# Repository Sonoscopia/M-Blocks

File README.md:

# M-Blocks
Modular MIDI Controllers

## INFO
M-Blocks is a projected developed by Sonoscopia Associação Cultural (www.sonoscopia.pt). 
It consists of several MIDI controllers (M-Controllers) that can be patched to a receiving interface (M-Brain) in a modular fashion, that is, connecting an arbitrary number (32 max.) and type of controllers such as buttons, knobs, faders, encoders, etc. 
The M-Brain than receives data from all the controllers via and maps them to MIDI messages sent to the output, either through USB (future implementation) or MIDI DIN connections.
The communication between modules is made using I2C (Inter-Integrated Circuit) using the Arduino platform (www.arduino.cc).  

### Note to programmers
When programming an M-Brain for the first time do not forget to set the EEPROM memory using /utilities/EEPROM_Preset_Clear/

## CHANGELOG

### version 0.1.2 (phobosfeijoada)
Fully functional M-Brain prototype and M-Controllers.
Continuous controls (ex: knobs) can now output notes, [see commit](https://github.com/Sonoscopia/M-Blocks/commit/bef133f0ddcc1b52bf48fc73a7da5345fef3f352).
M-Toggle code was modified to (MToggleAsButton) acting as M-Button to work with Phobos.
There are still some bugs when programming M-Brain but it works as long as one follows the manual and pays attention to the LED's.

### version 0.1.1 (francesinha)
Fully functional M-Brain prototype and M-Controllers. Needs testing...

### version 0.1.0 (protobrain)
First working version for M-Brain protoype version (the version with LED's instead of a screen). 

### version 0.0.3 (gopro)
As the code for M-Brain is getting bigger I moved the code development to Atmel Studio. In the 'firmware' folder should be a version to compile in Arduino IDE for those of you who don't have Atmel Studio. 

### version 0.0.2 (whoisthemaster)
Inverted Master/Slave relationship. 
Now M-Brain is the slave and M-Controllers are masters.
This way the controllers send data whenever their hardware sensor data changes, while the slave (M-Brain) is requested to read this data. 

### version 0.0.1 (first prototype)
First working sketch containing two modules (MBrain and MToggle).
In this version the controller (MToggle) acts as a Slave device and MBrain acts as a Master device, where the slave is constantly sending data to the master with a flag to let the master know if data has changed or not. 

## CONTRIBUTORS 
Contributors: Gustavo Costa, Tiago Ângelo, Rui Dias, Ján Solčáni and PierrePierrePierre.

## DEPENDENCIES & ACKNOWLEDGEMENTS
- Wire library (https://www.arduino.cc/en/reference/wire) 
- EEPROM library (https://www.arduino.cc/en/Reference/EEPROM)
- Rotary library by Ben Buxton(https://github.com/brianlow/Rotary)
- MIDI Library by François Best (https://github.com/FortySevenEffects/arduino_midi_library)
- TimerOne Library (https://www.arduino.cc/reference/en/libraries/timerone/)

## LICENSE
[![CC BY-NC 4.0][cc-by-nc-shield]][cc-by-nc]

This work is licensed under a
[Creative Commons Attribution-NonCommercial 4.0 International License][cc-by-nc].

[![CC BY-NC 4.0][cc-by-nc-image]][cc-by-nc]

[cc-by-nc]: https://creativecommons.org/licenses/by-nc/4.0/
[cc-by-nc-image]: https://licensebuttons.net/l/by-nc/4.0/88x31.png
[cc-by-nc-shield]: https://img.shields.io/badge/License-CC%20BY--NC%204.0-lightgrey.svg

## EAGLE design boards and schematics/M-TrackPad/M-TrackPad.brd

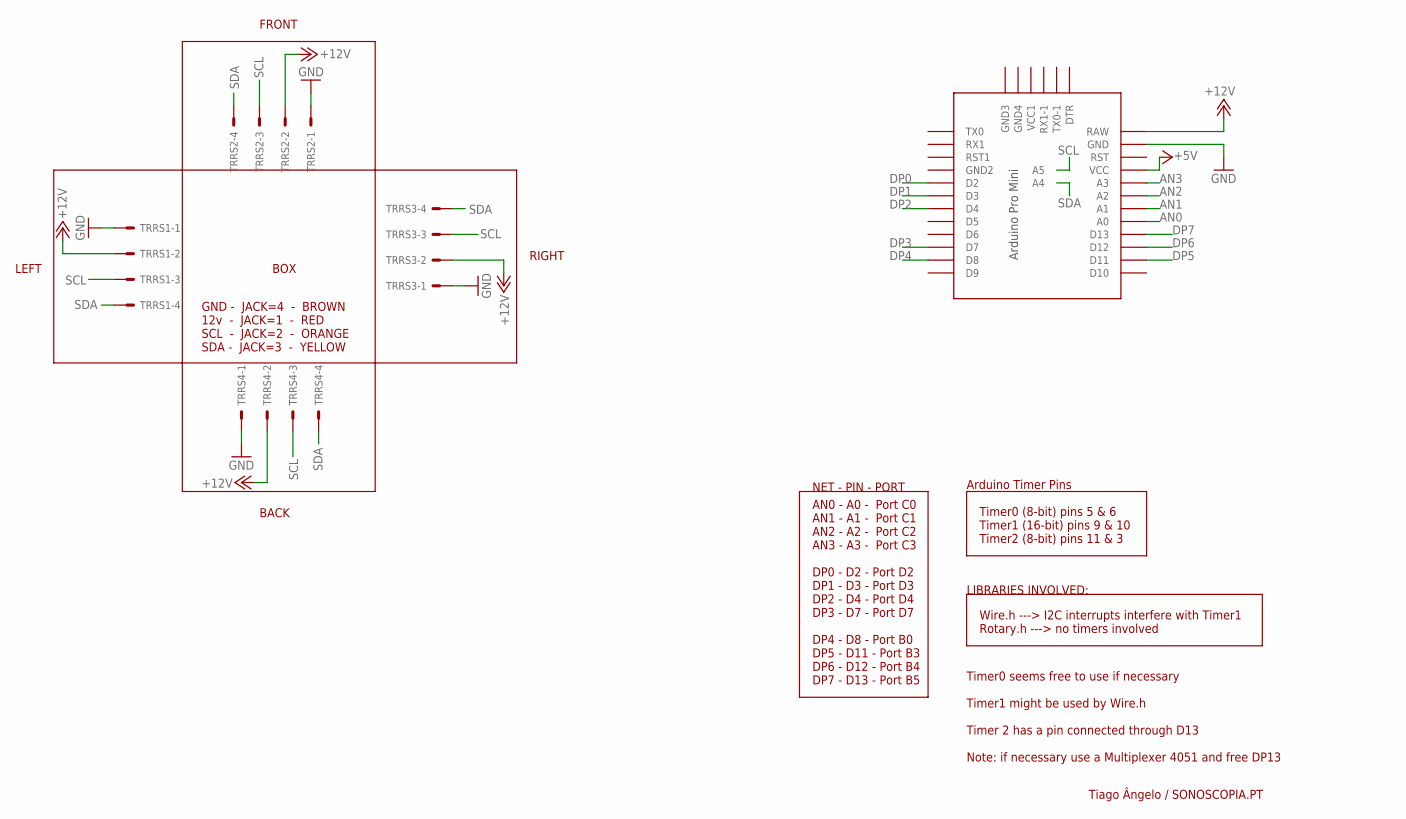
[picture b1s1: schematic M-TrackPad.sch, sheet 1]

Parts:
TRRS1, TRRS2, TRRS3, TRRS4: 22-27-2041-04; 6410-04
U$1: PRO-MINI-2

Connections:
+5V: U$1.VCC; also elsewhere on the board
+12V: TRRS1.2, TRRS2.2, TRRS3.2, TRRS4.2, U$1.RAW
AN0: U$1.A0
AN1: U$1.A1
AN2: U$1.A2
AN3: U$1.A3
DP0: U$1.D2; also elsewhere on the board
DP1: U$1.D3
DP2: U$1.D4
DP3: U$1.D7
DP4: U$1.D8
DP5: U$1.D11
DP6: U$1.D12
DP7: U$1.D13
GND: TRRS1.1, TRRS2.1, TRRS3.1, TRRS4.1, U$1.GND; also elsewhere on the board
SCL: TRRS1.3, TRRS2.3, TRRS3.3, TRRS4.3, U$1.A5; also elsewhere on the board
SDA: TRRS1.4, TRRS2.4, TRRS3.4, TRRS4.4, U$1.A4; also elsewhere on the board

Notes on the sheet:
Timer0 (8-bit) pins 5 & 6 Timer1 (16-bit) pins 9 & 10 Timer2 (8-bit) pins 11 & 3
Arduino Timer Pins
AN0 - A0 - Port C0 AN1 - A1 - Port C1 AN2 - A2 - Port C2 AN3 - A3 - Port C3 DP0 - D2 - Port D2 DP1 - D3 - Port D3 DP2 - D4 - Port D4 DP3 - D7 - Port D7 DP4 - D8 - Port B0 DP5 - D11 - Port B3 DP6 - D12 - Port B4 DP7 - D13 - Port B5
Wire.h ---> I2C interrupts interfere with Timer1 Rotary.h ---> no timers involved
LIBRARIES INVOLVED:
NET - PIN - PORT
Timer0 seems free to use if necessary Timer1 might be used by Wire.h Timer 2 has a pin connected through D13 Note: if necessary use a Multiplexer 4051 and free DP13
BOX
FRONT
RIGHT
LEFT
BACK
GND - JACK=4 - BROWN 12v - JACK=1 - RED SCL - JACK=2 - ORANGE SDA - JACK=3 - YELLOW
Tiago Ângelo / SONOSCOPIA.PT

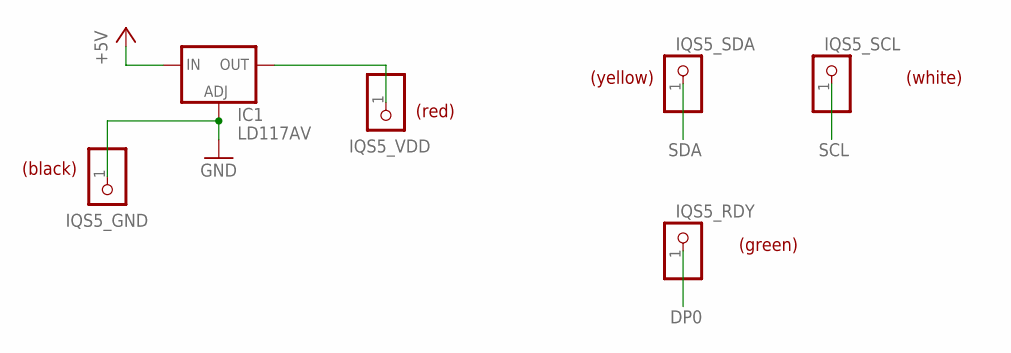
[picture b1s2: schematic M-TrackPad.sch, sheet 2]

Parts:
IC1: LD117AV; TO220L1
IQS5_GND, IQS5_RDY, IQS5_SCL, IQS5_SDA, IQS5_VDD: PINHD-1X1; 1X01

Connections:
+5V: IC1.3 (IN); also elsewhere on the board
DP0: IQS5_RDY.1; also elsewhere on the board
GND: IC1.1 (ADJ), IQS5_GND.1; also elsewhere on the board
unnamed: IC1.2 (OUT), IQS5_VDD.1
SCL: IQS5_SCL.1; also elsewhere on the board
SDA: IQS5_SDA.1; also elsewhere on the board

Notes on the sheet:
(black)
(red)
(yellow)
(white)
(green)

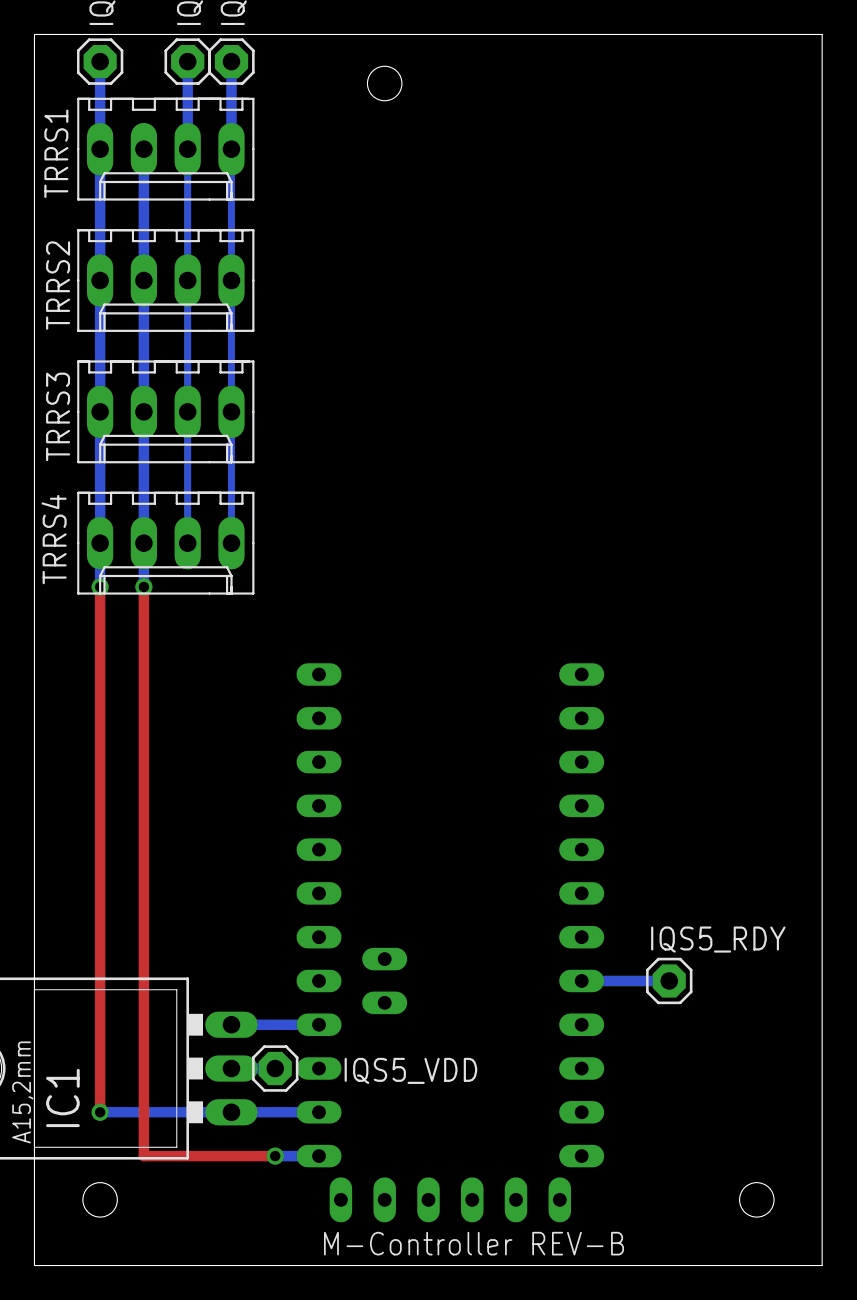
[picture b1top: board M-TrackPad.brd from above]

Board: 2 copper layers, 45.7 x 71.4 mm, 11 parts (0 on the bottom side), 7 nets.

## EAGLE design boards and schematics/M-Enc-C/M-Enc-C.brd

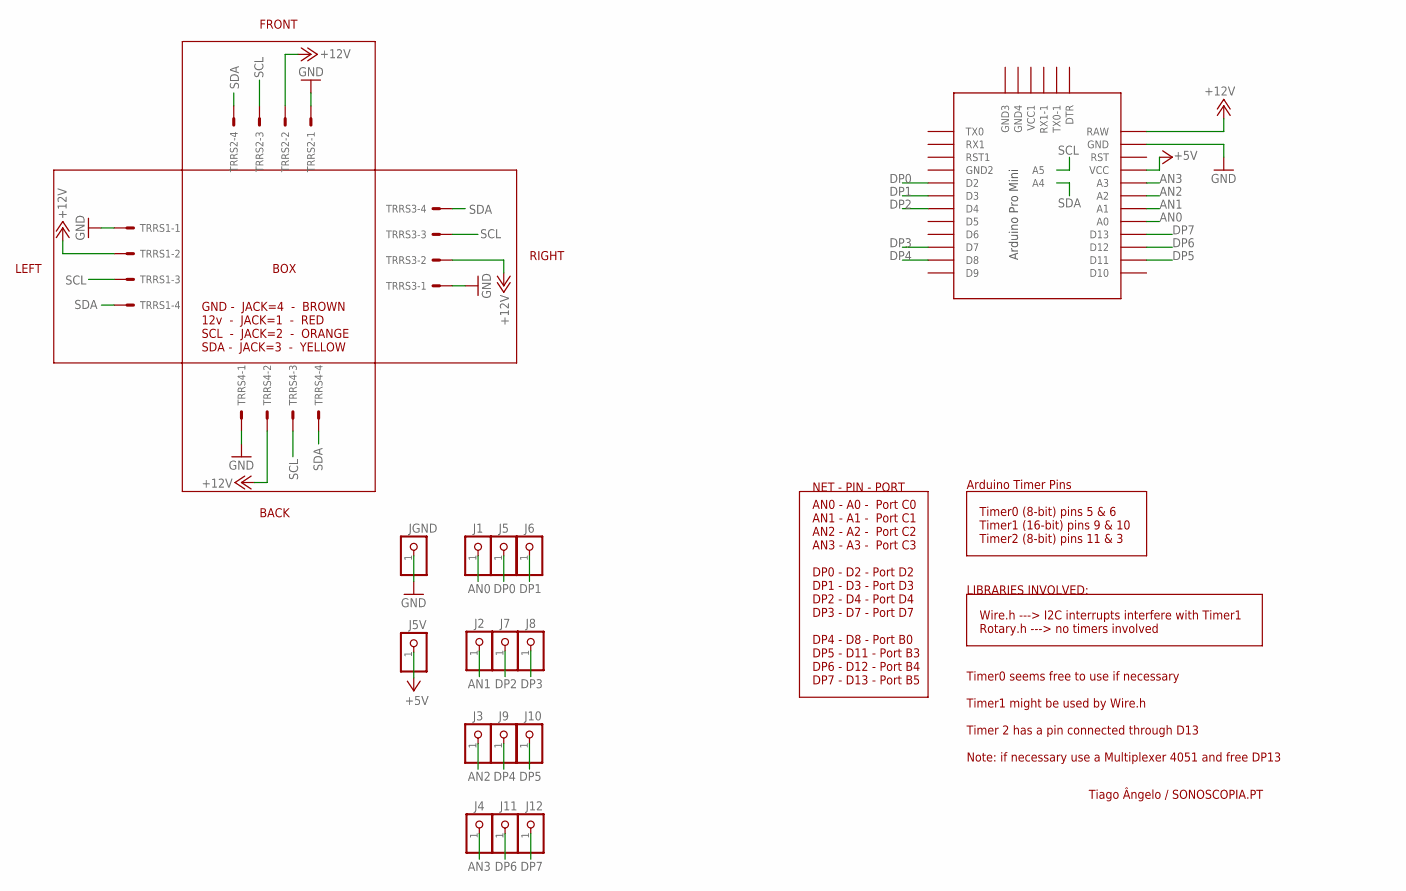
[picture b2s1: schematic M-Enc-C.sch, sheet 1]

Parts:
J1, J2, J3, J4, J5, J5V, J6, J7, J8, J9, J10, J11, J12: PINHD-1X1; 1X01
JGND: PINHD-1X1; 1X01
TRRS1, TRRS2, TRRS3, TRRS4: 22-27-2041-04; 6410-04
U$1: PRO-MINI-2

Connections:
+5V: J5V.1, U$1.VCC
+12V: TRRS1.2, TRRS2.2, TRRS3.2, TRRS4.2, U$1.RAW
AN0: J1.1, U$1.A0
AN1: J2.1, U$1.A1
AN2: J3.1, U$1.A2
AN3: J4.1, U$1.A3
DP0: J5.1, U$1.D2
DP1: J6.1, U$1.D3
DP2: J7.1, U$1.D4
DP3: J8.1, U$1.D7
DP4: J9.1, U$1.D8
DP5: J10.1, U$1.D11
DP6: J11.1, U$1.D12
DP7: J12.1, U$1.D13
GND: JGND.1, TRRS1.1, TRRS2.1, TRRS3.1, TRRS4.1, U$1.GND
SCL: TRRS1.3, TRRS2.3, TRRS3.3, TRRS4.3, U$1.A5
SDA: TRRS1.4, TRRS2.4, TRRS3.4, TRRS4.4, U$1.A4

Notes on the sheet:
Timer0 (8-bit) pins 5 & 6 Timer1 (16-bit) pins 9 & 10 Timer2 (8-bit) pins 11 & 3
Arduino Timer Pins
AN0 - A0 - Port C0 AN1 - A1 - Port C1 AN2 - A2 - Port C2 AN3 - A3 - Port C3 DP0 - D2 - Port D2 DP1 - D3 - Port D3 DP2 - D4 - Port D4 DP3 - D7 - Port D7 DP4 - D8 - Port B0 DP5 - D11 - Port B3 DP6 - D12 - Port B4 DP7 - D13 - Port B5
Wire.h ---> I2C interrupts interfere with Timer1 Rotary.h ---> no timers involved
LIBRARIES INVOLVED:
NET - PIN - PORT
Timer0 seems free to use if necessary Timer1 might be used by Wire.h Timer 2 has a pin connected through D13 Note: if necessary use a Multiplexer 4051 and free DP13
BOX
FRONT
RIGHT
LEFT
BACK
GND - JACK=4 - BROWN 12v - JACK=1 - RED SCL - JACK=2 - ORANGE SDA - JACK=3 - YELLOW
Tiago Ângelo / SONOSCOPIA.PT

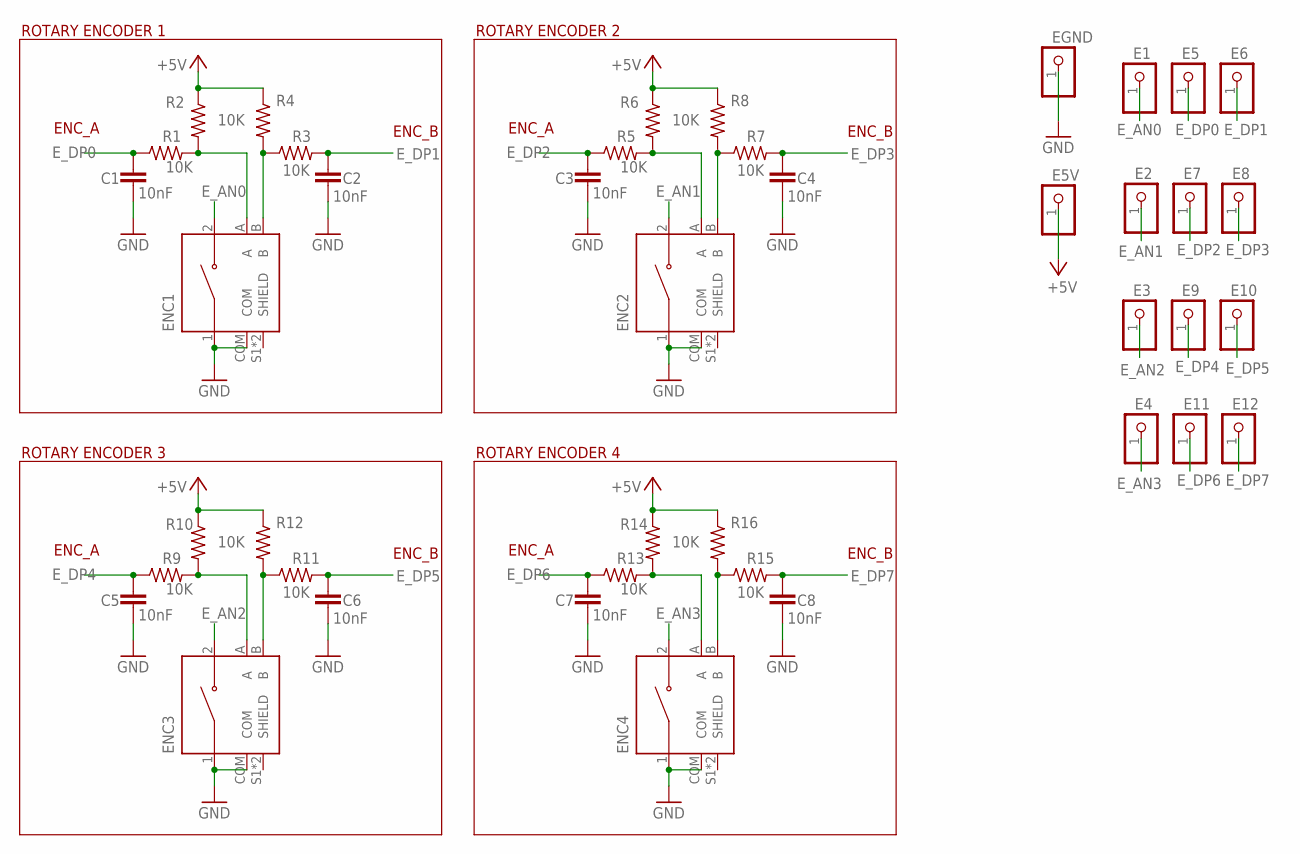
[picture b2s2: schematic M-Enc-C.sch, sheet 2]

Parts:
C1, C3: 10nF; C5B2.5
C2, C4, C5, C7: 10nF; C10B4
C6, C8: 10nF; C2.5-2
E1, E2, E3, E4, E5, E5V, E6, E7, E8, E9, E10, E11, E12: PINHD-1X1; 1X01
EGND: PINHD-1X1; 1X01
ENC1, ENC2, ENC3, ENC4: PEC11R-4215F-S0024; XDCR_PEC11R-4215F-S0024
R1, R2, R3, R5, R6, R7, R9, R11, R12, R13, R15, R16: 10K; 0204/7
R4, R8, R10, R14: 10K; 0207/12

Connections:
E_+5V: E5V.1, R2.1, R4.1, R6.1, R8.1, R10.1, R12.1, R14.1, R16.1
E_AN0: E1.1, ENC1.2
E_AN1: E2.1, ENC2.2
E_AN2: E3.1, ENC3.2
E_AN3: E4.1, ENC4.2
E_DP0: C1.1, E5.1, R1.1
E_DP1: C2.1, E6.1, R3.2
E_DP2: C3.1, E7.1, R5.1
E_DP3: C4.1, E8.1, R7.2
E_DP4: C5.1, E9.1, R9.1
E_DP5: C6.1, E10.1, R11.2
E_DP6: C7.1, E11.1, R13.1
E_DP7: C8.1, E12.1, R15.2
E_GND: C1.2, C2.2, C3.2, C4.2, C5.2, C6.2, C7.2, C8.2, EGND.1, ENC1.1, ENC1.COM, ENC2.1, ENC2.COM, ENC3.1, ENC3.COM, ENC4.1, ENC4.COM
unnamed: ENC2.A, R5.2, R6.2
unnamed: ENC1.B, R3.1, R4.2
unnamed: ENC2.B, R7.1, R8.2
unnamed: ENC3.A, R9.2, R10.2
unnamed: ENC3.B, R11.1, R12.2
unnamed: ENC4.A, R13.2, R14.2
unnamed: ENC4.B, R15.1, R16.2
unnamed: ENC1.A, R1.2, R2.2

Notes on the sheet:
ROTARY ENCODER 1
ENC_A
ENC_B
ROTARY ENCODER 2
ROTARY ENCODER 3
ROTARY ENCODER 4

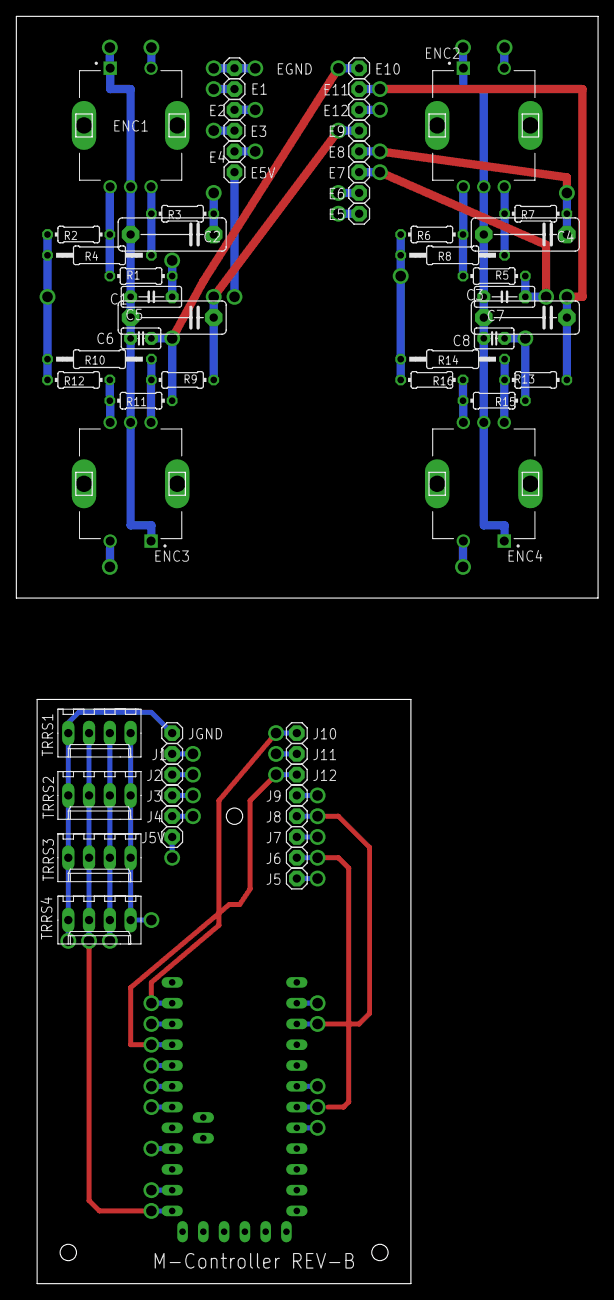
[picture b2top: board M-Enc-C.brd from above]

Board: 7 copper layers, 71.1 x 154.9 mm, 61 parts (0 on the bottom side), 39 nets.

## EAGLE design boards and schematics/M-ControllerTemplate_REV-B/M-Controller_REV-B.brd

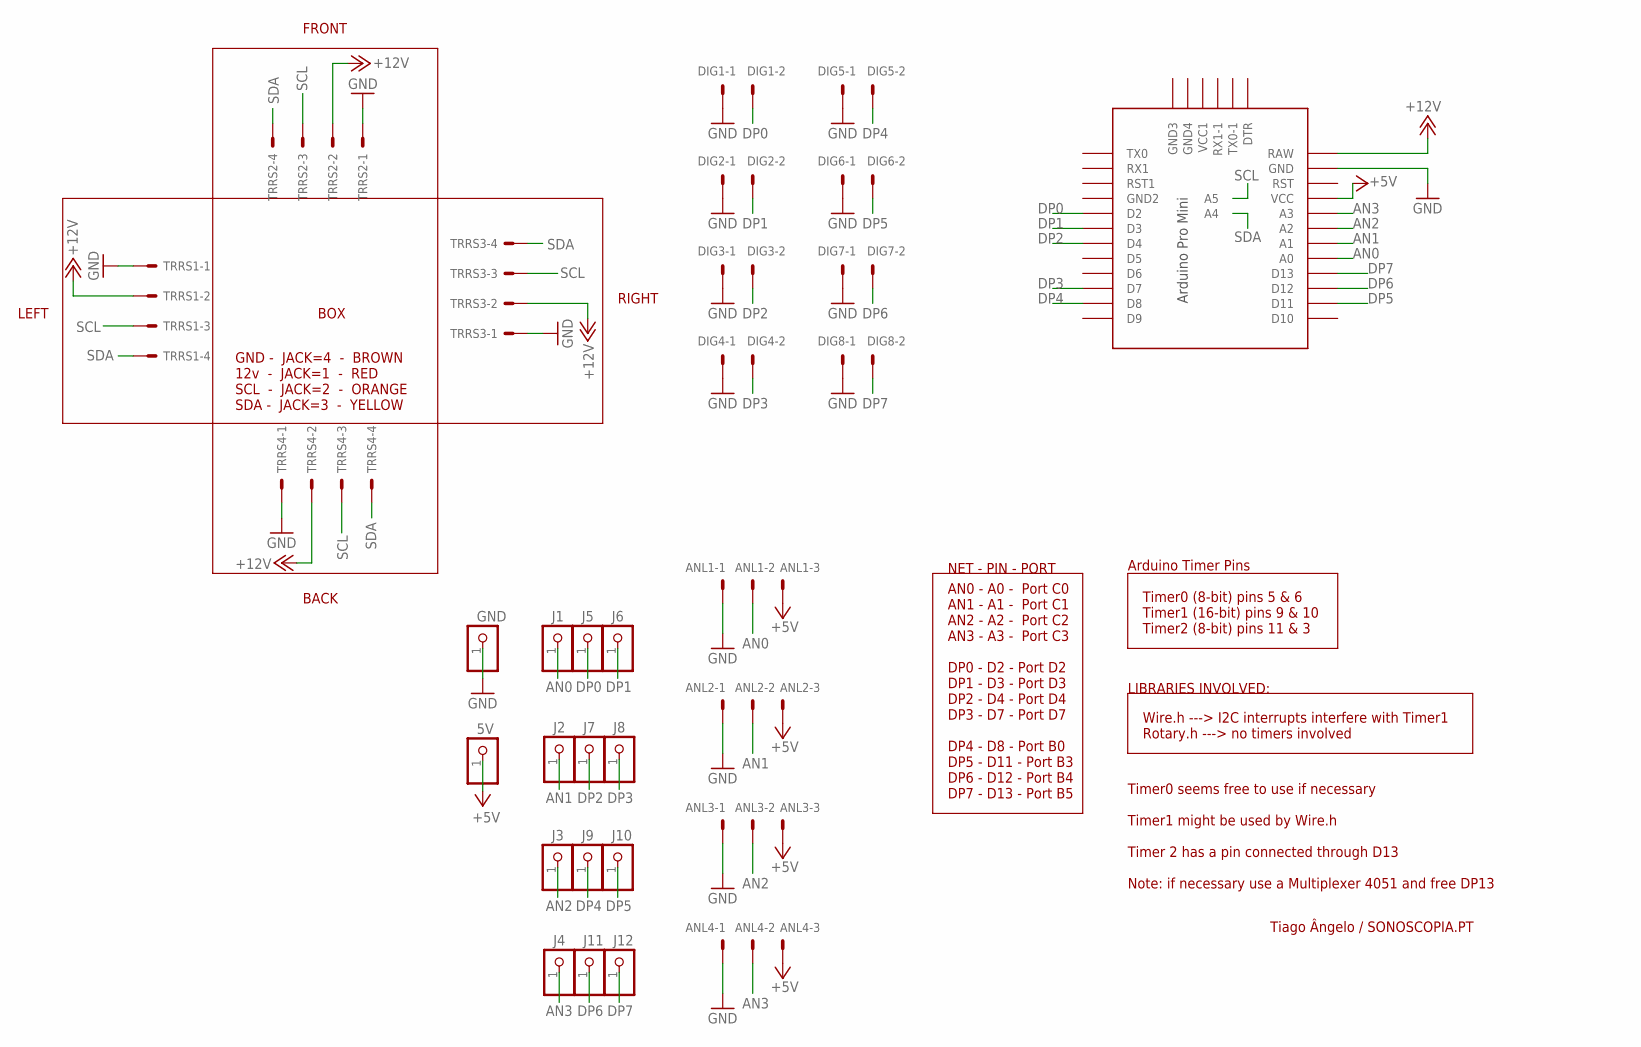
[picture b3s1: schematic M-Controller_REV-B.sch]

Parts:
5V: PINHD-1X1; 1X01
ANL1, ANL2, ANL3, ANL4: 22-27-2031-03; 6410-03
DIG1, DIG2, DIG3, DIG4, DIG5, DIG6, DIG7, DIG8: 22-27-2021-02; 6410-02
GND: PINHD-1X1; 1X01
J1, J2, J3, J4, J5, J6, J7, J8, J9, J10, J11, J12: PINHD-1X1; 1X01
TRRS1, TRRS2, TRRS3, TRRS4: 22-27-2041-04; 6410-04
U$1: PRO-MINI-2

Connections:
+5V: 5V.1, ANL1.3, ANL2.3, ANL3.3, ANL4.3, U$1.VCC
+12V: TRRS1.2, TRRS2.2, TRRS3.2, TRRS4.2, U$1.RAW
AN0: ANL1.2, J1.1, U$1.A0
AN1: ANL2.2, J2.1, U$1.A1
AN2: ANL3.2, J3.1, U$1.A2
AN3: ANL4.2, J4.1, U$1.A3
DP0: DIG1.2, J5.1, U$1.D2
DP1: DIG2.2, J6.1, U$1.D3
DP2: DIG3.2, J7.1, U$1.D4
DP3: DIG4.2, J8.1, U$1.D7
DP4: DIG5.2, J9.1, U$1.D8
DP5: DIG6.2, J10.1, U$1.D11
DP6: DIG7.2, J11.1, U$1.D12
DP7: DIG8.2, J12.1, U$1.D13
GND: ANL1.1, ANL2.1, ANL3.1, ANL4.1, DIG1.1, DIG2.1, DIG3.1, DIG4.1, DIG5.1, DIG6.1, DIG7.1, DIG8.1, GND.1, TRRS1.1, TRRS2.1, TRRS3.1, TRRS4.1, U$1.GND
SCL: TRRS1.3, TRRS2.3, TRRS3.3, TRRS4.3, U$1.A5
SDA: TRRS1.4, TRRS2.4, TRRS3.4, TRRS4.4, U$1.A4

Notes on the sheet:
Timer0 (8-bit) pins 5 & 6 Timer1 (16-bit) pins 9 & 10 Timer2 (8-bit) pins 11 & 3
Arduino Timer Pins
AN0 - A0 - Port C0 AN1 - A1 - Port C1 AN2 - A2 - Port C2 AN3 - A3 - Port C3 DP0 - D2 - Port D2 DP1 - D3 - Port D3 DP2 - D4 - Port D4 DP3 - D7 - Port D7 DP4 - D8 - Port B0 DP5 - D11 - Port B3 DP6 - D12 - Port B4 DP7 - D13 - Port B5
Wire.h ---> I2C interrupts interfere with Timer1 Rotary.h ---> no timers involved
LIBRARIES INVOLVED:
NET - PIN - PORT
Timer0 seems free to use if necessary Timer1 might be used by Wire.h Timer 2 has a pin connected through D13 Note: if necessary use a Multiplexer 4051 and free DP13
BOX
FRONT
RIGHT
LEFT
BACK
GND - JACK=4 - BROWN 12v - JACK=1 - RED SCL - JACK=2 - ORANGE SDA - JACK=3 - YELLOW
Tiago Ângelo / SONOSCOPIA.PT

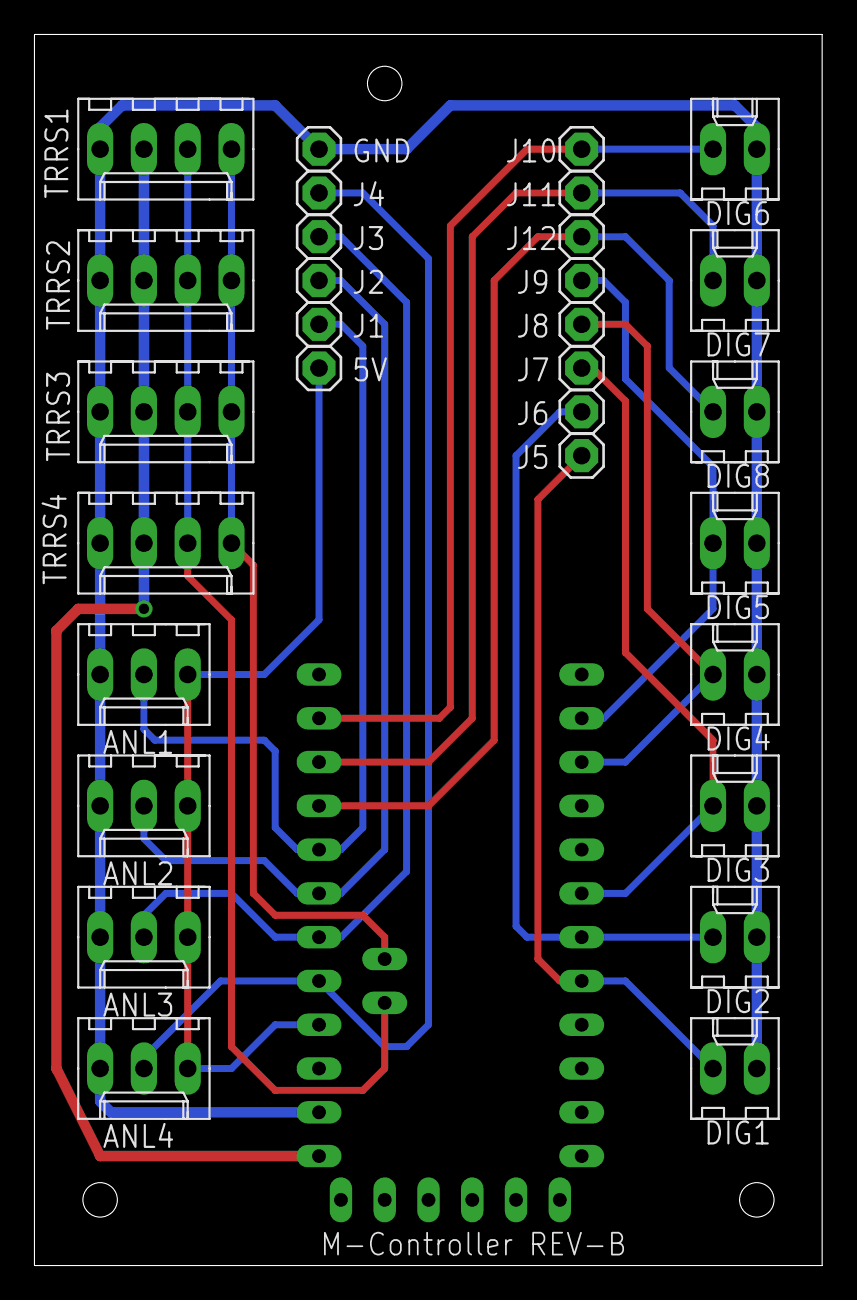
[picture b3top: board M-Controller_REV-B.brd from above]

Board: 2 copper layers, 45.7 x 71.4 mm, 31 parts (0 on the bottom side), 17 nets.

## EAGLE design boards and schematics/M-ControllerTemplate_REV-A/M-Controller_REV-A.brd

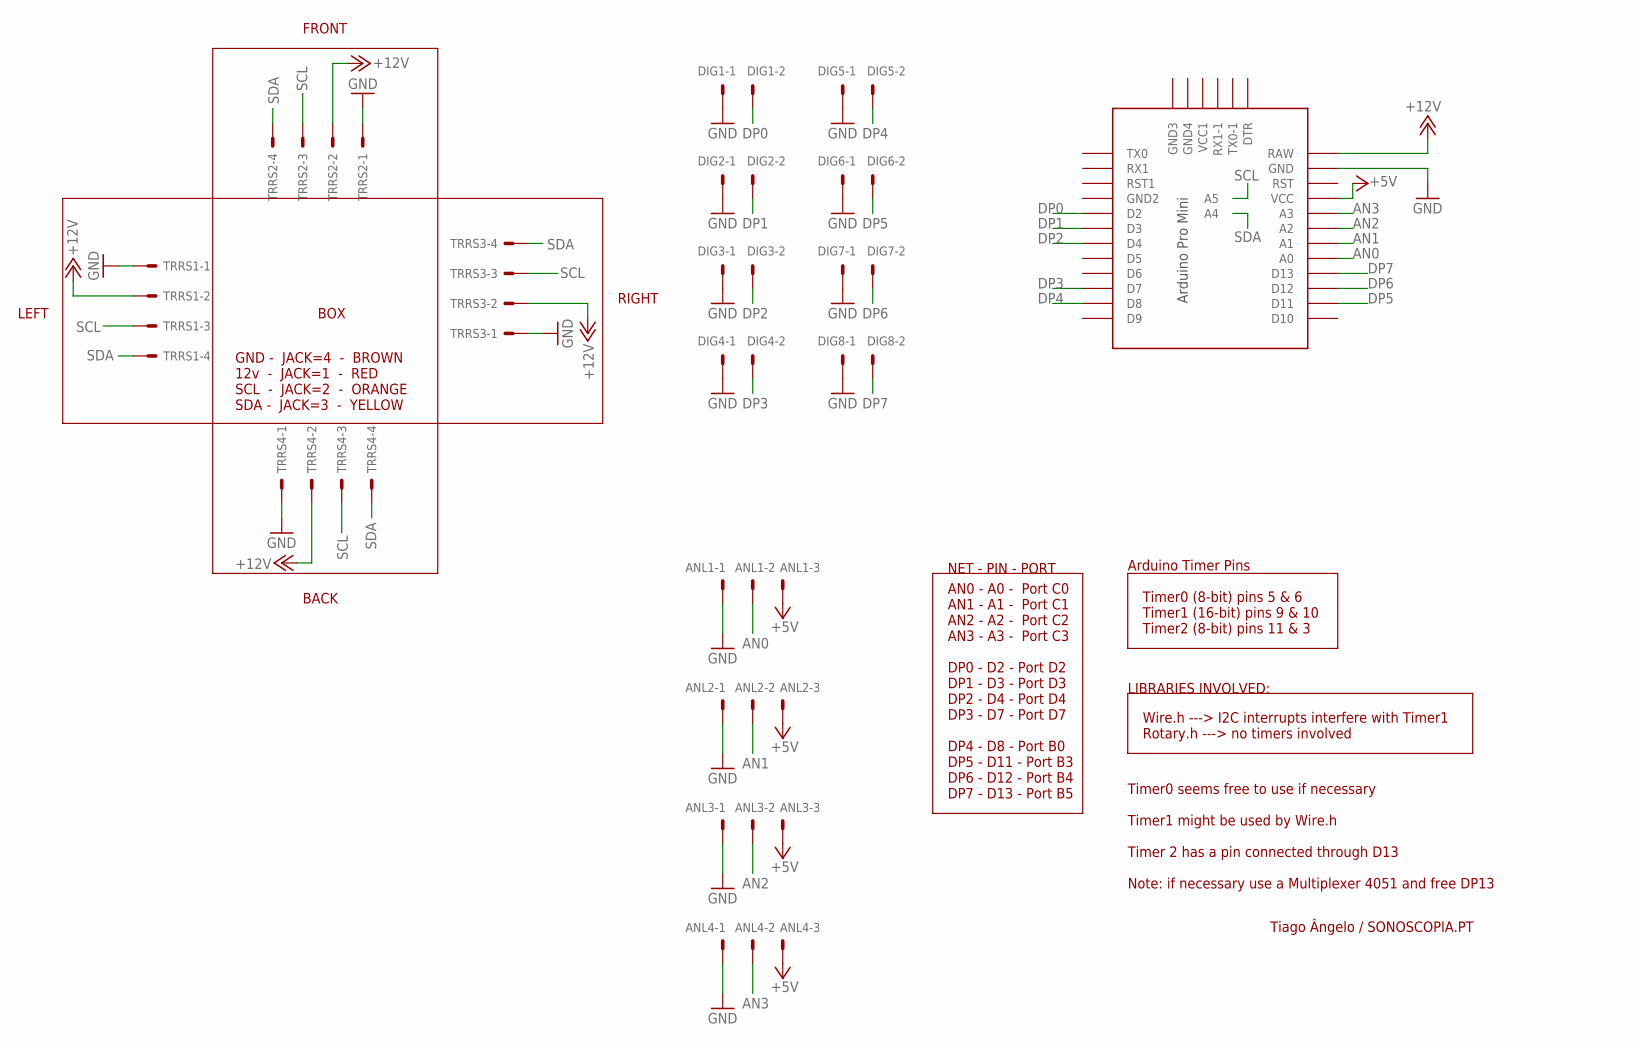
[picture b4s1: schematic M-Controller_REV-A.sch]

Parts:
ANL1, ANL2, ANL3, ANL4: 22-27-2031-03; 6410-03
DIG1, DIG2, DIG3, DIG4, DIG5, DIG6, DIG7, DIG8: 22-27-2021-02; 6410-02
TRRS1, TRRS2, TRRS3, TRRS4: 22-27-2041-04; 6410-04
U$1: PRO-MINI-2

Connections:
+5V: ANL1.3, ANL2.3, ANL3.3, ANL4.3, U$1.VCC
+12V: TRRS1.2, TRRS2.2, TRRS3.2, TRRS4.2, U$1.RAW
AN0: ANL1.2, U$1.A0
AN1: ANL2.2, U$1.A1
AN2: ANL3.2, U$1.A2
AN3: ANL4.2, U$1.A3
DP0: DIG1.2, U$1.D2
DP1: DIG2.2, U$1.D3
DP2: DIG3.2, U$1.D4
DP3: DIG4.2, U$1.D7
DP4: DIG5.2, U$1.D8
DP5: DIG6.2, U$1.D11
DP6: DIG7.2, U$1.D12
DP7: DIG8.2, U$1.D13
GND: ANL1.1, ANL2.1, ANL3.1, ANL4.1, DIG1.1, DIG2.1, DIG3.1, DIG4.1, DIG5.1, DIG6.1, DIG7.1, DIG8.1, TRRS1.1, TRRS2.1, TRRS3.1, TRRS4.1, U$1.GND
SCL: TRRS1.3, TRRS2.3, TRRS3.3, TRRS4.3, U$1.A5
SDA: TRRS1.4, TRRS2.4, TRRS3.4, TRRS4.4, U$1.A4

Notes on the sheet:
Timer0 (8-bit) pins 5 & 6 Timer1 (16-bit) pins 9 & 10 Timer2 (8-bit) pins 11 & 3
Arduino Timer Pins
AN0 - A0 - Port C0 AN1 - A1 - Port C1 AN2 - A2 - Port C2 AN3 - A3 - Port C3 DP0 - D2 - Port D2 DP1 - D3 - Port D3 DP2 - D4 - Port D4 DP3 - D7 - Port D7 DP4 - D8 - Port B0 DP5 - D11 - Port B3 DP6 - D12 - Port B4 DP7 - D13 - Port B5
Wire.h ---> I2C interrupts interfere with Timer1 Rotary.h ---> no timers involved
LIBRARIES INVOLVED:
NET - PIN - PORT
Timer0 seems free to use if necessary Timer1 might be used by Wire.h Timer 2 has a pin connected through D13 Note: if necessary use a Multiplexer 4051 and free DP13
BOX
FRONT
RIGHT
LEFT
BACK
GND - JACK=4 - BROWN 12v - JACK=1 - RED SCL - JACK=2 - ORANGE SDA - JACK=3 - YELLOW
Tiago Ângelo / SONOSCOPIA.PT

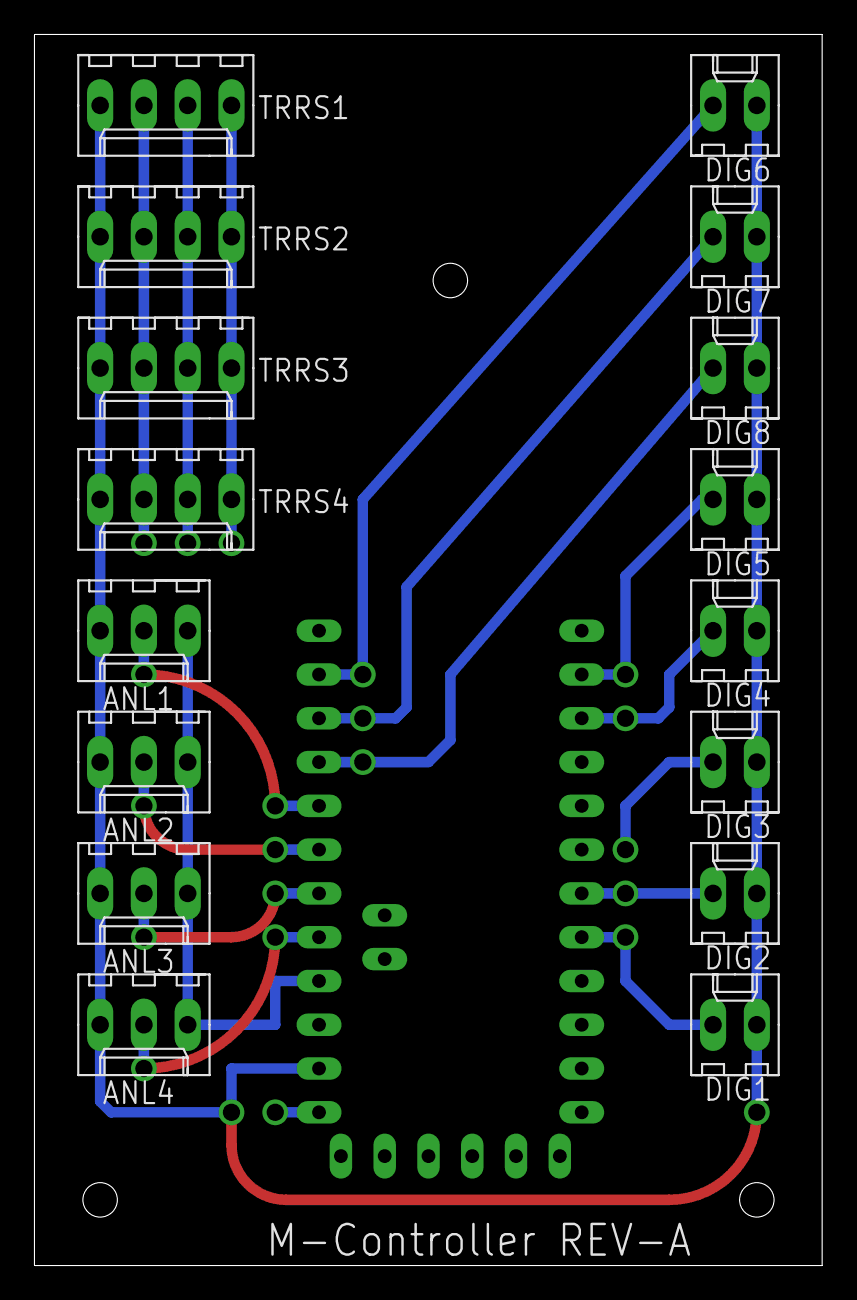
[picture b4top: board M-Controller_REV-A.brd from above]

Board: 2 copper layers, 45.7 x 71.4 mm, 17 parts (0 on the bottom side), 17 nets.

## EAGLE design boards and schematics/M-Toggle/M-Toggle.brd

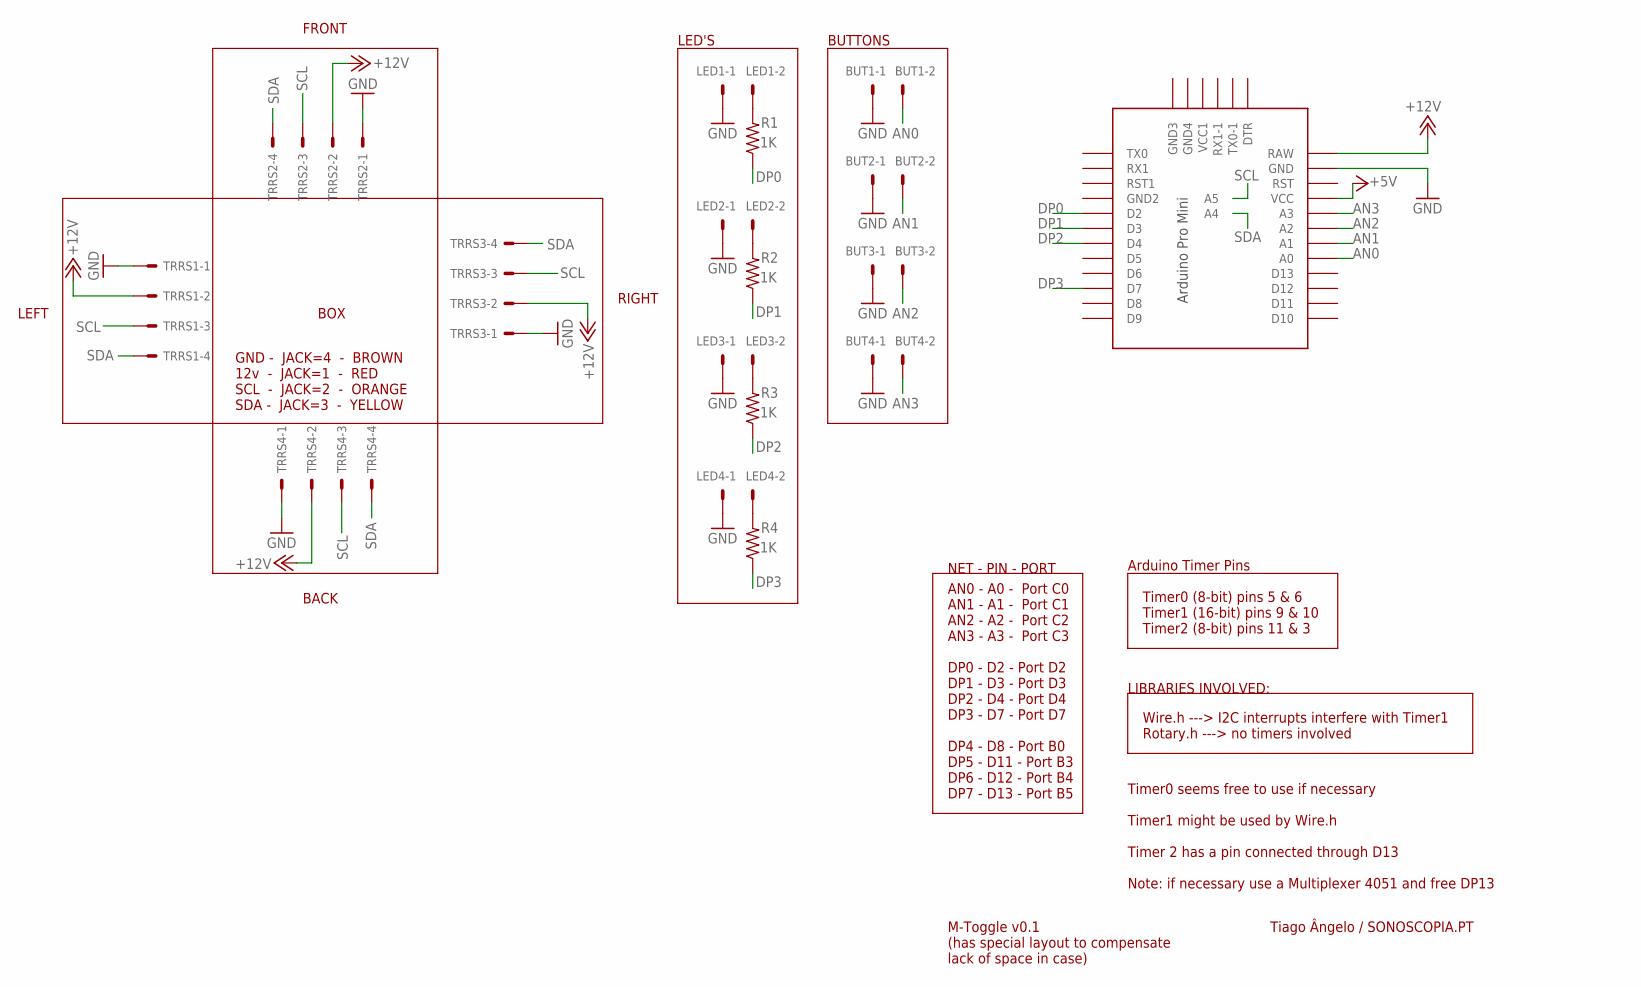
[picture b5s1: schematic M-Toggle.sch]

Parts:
BUT1, BUT2, BUT3, BUT4: 22-27-2021-02; 6410-02
LED1, LED2, LED3, LED4: 22-27-2021-02; 6410-02
R1, R2, R3, R4: 1K; 0204/7
TRRS1, TRRS2, TRRS3, TRRS4: 22-27-2041-04; 6410-04
U$1: PRO-MINI-2

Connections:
+5V: U$1.VCC
+12V: TRRS1.2, TRRS2.2, TRRS3.2, TRRS4.2, U$1.RAW
AN0: BUT1.2, U$1.A0
AN1: BUT2.2, U$1.A1
AN2: BUT3.2, U$1.A2
AN3: BUT4.2, U$1.A3
DP0: R1.1, U$1.D2
DP1: R2.1, U$1.D3
DP2: R3.1, U$1.D4
DP3: R4.1, U$1.D7
GND: BUT1.1, BUT2.1, BUT3.1, BUT4.1, LED1.1, LED2.1, LED3.1, LED4.1, TRRS1.1, TRRS2.1, TRRS3.1, TRRS4.1, U$1.GND
unnamed: LED1.2, R1.2
unnamed: LED2.2, R2.2
unnamed: LED3.2, R3.2
unnamed: LED4.2, R4.2
SCL: TRRS1.3, TRRS2.3, TRRS3.3, TRRS4.3, U$1.A5
SDA: TRRS1.4, TRRS2.4, TRRS3.4, TRRS4.4, U$1.A4

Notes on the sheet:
Timer0 (8-bit) pins 5 & 6 Timer1 (16-bit) pins 9 & 10 Timer2 (8-bit) pins 11 & 3
Arduino Timer Pins
AN0 - A0 - Port C0 AN1 - A1 - Port C1 AN2 - A2 - Port C2 AN3 - A3 - Port C3 DP0 - D2 - Port D2 DP1 - D3 - Port D3 DP2 - D4 - Port D4 DP3 - D7 - Port D7 DP4 - D8 - Port B0 DP5 - D11 - Port B3 DP6 - D12 - Port B4 DP7 - D13 - Port B5
Wire.h ---> I2C interrupts interfere with Timer1 Rotary.h ---> no timers involved
LIBRARIES INVOLVED:
NET - PIN - PORT
Timer0 seems free to use if necessary Timer1 might be used by Wire.h Timer 2 has a pin connected through D13 Note: if necessary use a Multiplexer 4051 and free DP13
BOX
FRONT
RIGHT
LEFT
BACK
GND - JACK=4 - BROWN 12v - JACK=1 - RED SCL - JACK=2 - ORANGE SDA - JACK=3 - YELLOW
LED'S
BUTTONS
M-Toggle v0.1 (has special layout to compensate lack of space in case)
Tiago Ângelo / SONOSCOPIA.PT

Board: 2 copper layers, 17 parts (0 on the bottom side), 16 nets, no tracks yet.

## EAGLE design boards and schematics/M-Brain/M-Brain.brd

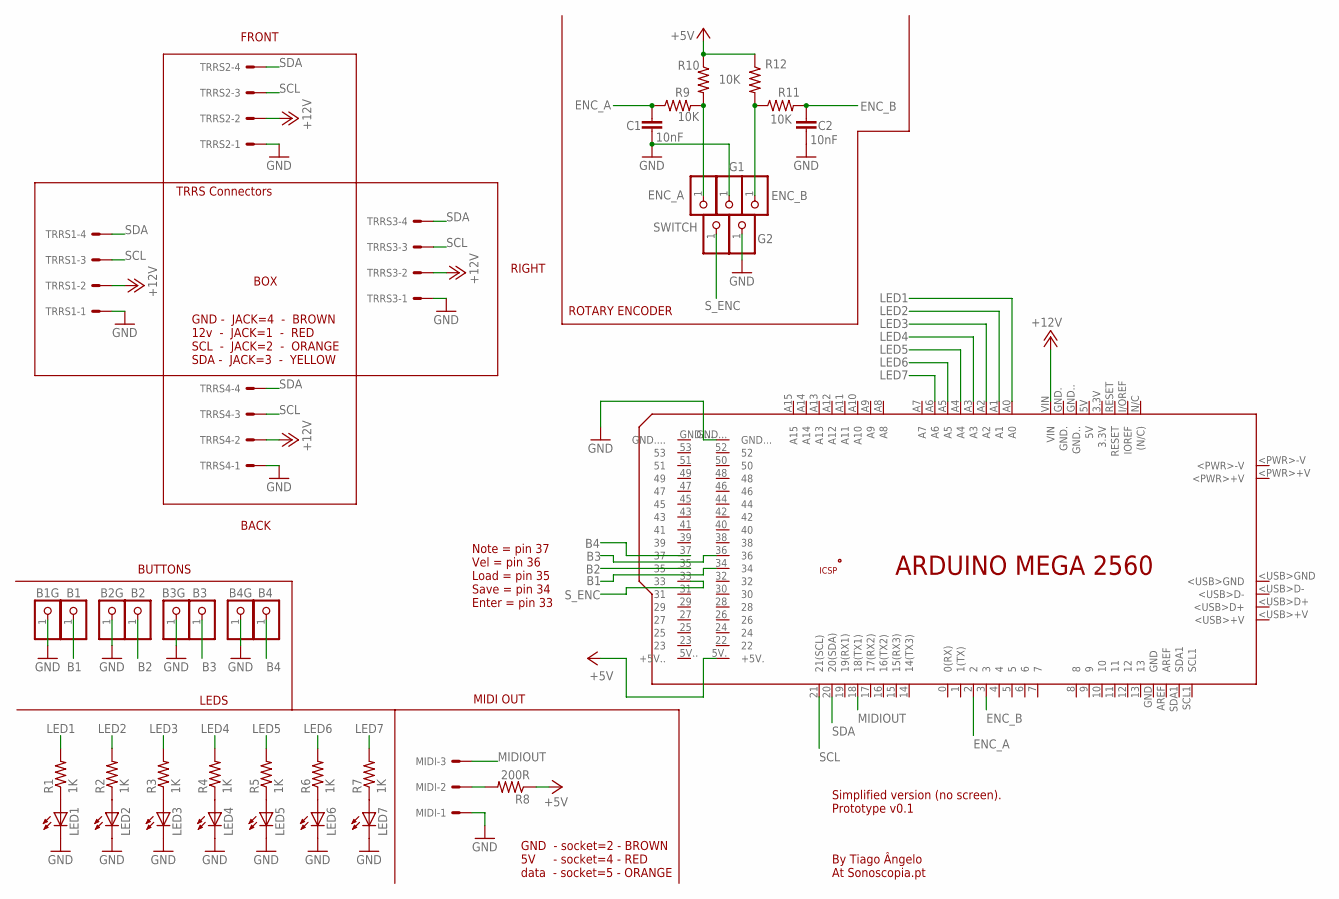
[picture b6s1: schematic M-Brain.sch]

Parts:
B1, B1G, B2, B2G, B3, B3G, B4, B4G: PINHD-1X1; 1X01
C1, C2: 10nF; C2.5-2
ENC_A: PINHD-1X1; 1X01
ENC_B: PINHD-1X1; 1X01
G1, G2: PINHD-1X1; 1X01
LED1, LED2, LED3, LED4, LED5, LED6, LED7: LED5MM
MIDI: 22-27-2031-03; 6410-03
PCB1: ARDUINO_MEGA2560
R1, R2, R3, R4, R5, R6, R7: 1K; 0204/5
R8: 200R; 0204/7
R9, R10, R11, R12: 10K; 0204/7
SWITCH: PINHD-1X1; 1X01
TRRS1, TRRS2, TRRS3, TRRS4: 22-27-2041-04; 6410-04

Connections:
+5V: PCB1.5V. (+5V.), R8.1, R10.1, R12.1
+12V: PCB1.VIN, TRRS1.2, TRRS2.2, TRRS3.2, TRRS4.2
B1: B1.1, PCB1.34
B2: B2.1, PCB1.35
B3: B3.1, PCB1.36
B4: B4.1, PCB1.37
ENC_A: C1.1, PCB1.2, R9.1
ENC_B: C2.1, PCB1.3, R11.2
GND: B1G.1, B2G.1, B3G.1, B4G.1, C1.2, C2.2, G1.1, G2.1, LED1.K (C), LED2.K (C), LED3.K (C), LED4.K (C), LED5.K (C), LED6.K (C), LED7.K (C), MIDI.1, PCB1.GND..., TRRS1.1, TRRS2.1, TRRS3.1, TRRS4.1
LED1: PCB1.A0, R1.2
LED2: PCB1.A1, R2.2
LED3: PCB1.A2, R3.2
LED4: PCB1.A3, R4.2
LED5: PCB1.A4, R5.2
LED6: PCB1.A5, R6.2
LED7: PCB1.A6, R7.2
MIDIOUT: MIDI.3, PCB1.18 (18(TX1))
unnamed: LED1.A, R1.1
unnamed: LED2.A, R2.1
unnamed: LED3.A, R3.1
unnamed: LED4.A, R4.1
unnamed: LED5.A, R5.1
unnamed: LED6.A, R6.1
unnamed: LED7.A, R7.1
unnamed: MIDI.2, R8.2
unnamed: ENC_A.1, R9.2, R10.2
unnamed: ENC_B.1, R11.1, R12.2
SCL: PCB1.21 (21(SCL)), TRRS1.3, TRRS2.3, TRRS3.3, TRRS4.3
SDA: PCB1.20 (20(SDA)), TRRS1.4, TRRS2.4, TRRS3.4, TRRS4.4
S_ENC: PCB1.33, SWITCH.1

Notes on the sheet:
Simplified version (no screen). Prototype v0.1
By Tiago Ângelo At Sonoscopia.pt
BOX
FRONT
RIGHT
BACK
BUTTONS
LEDS
MIDI OUT
ROTARY ENCODER
TRRS Connectors
Note = pin 37 Vel = pin 36 Load = pin 35 Save = pin 34 Enter = pin 33
GND - JACK=4 - BROWN 12v - JACK=1 - RED SCL - JACK=2 - ORANGE SDA - JACK=3 - YELLOW
GND - socket=2 - BROWN 5V - socket=4 - RED data - socket=5 - ORANGE

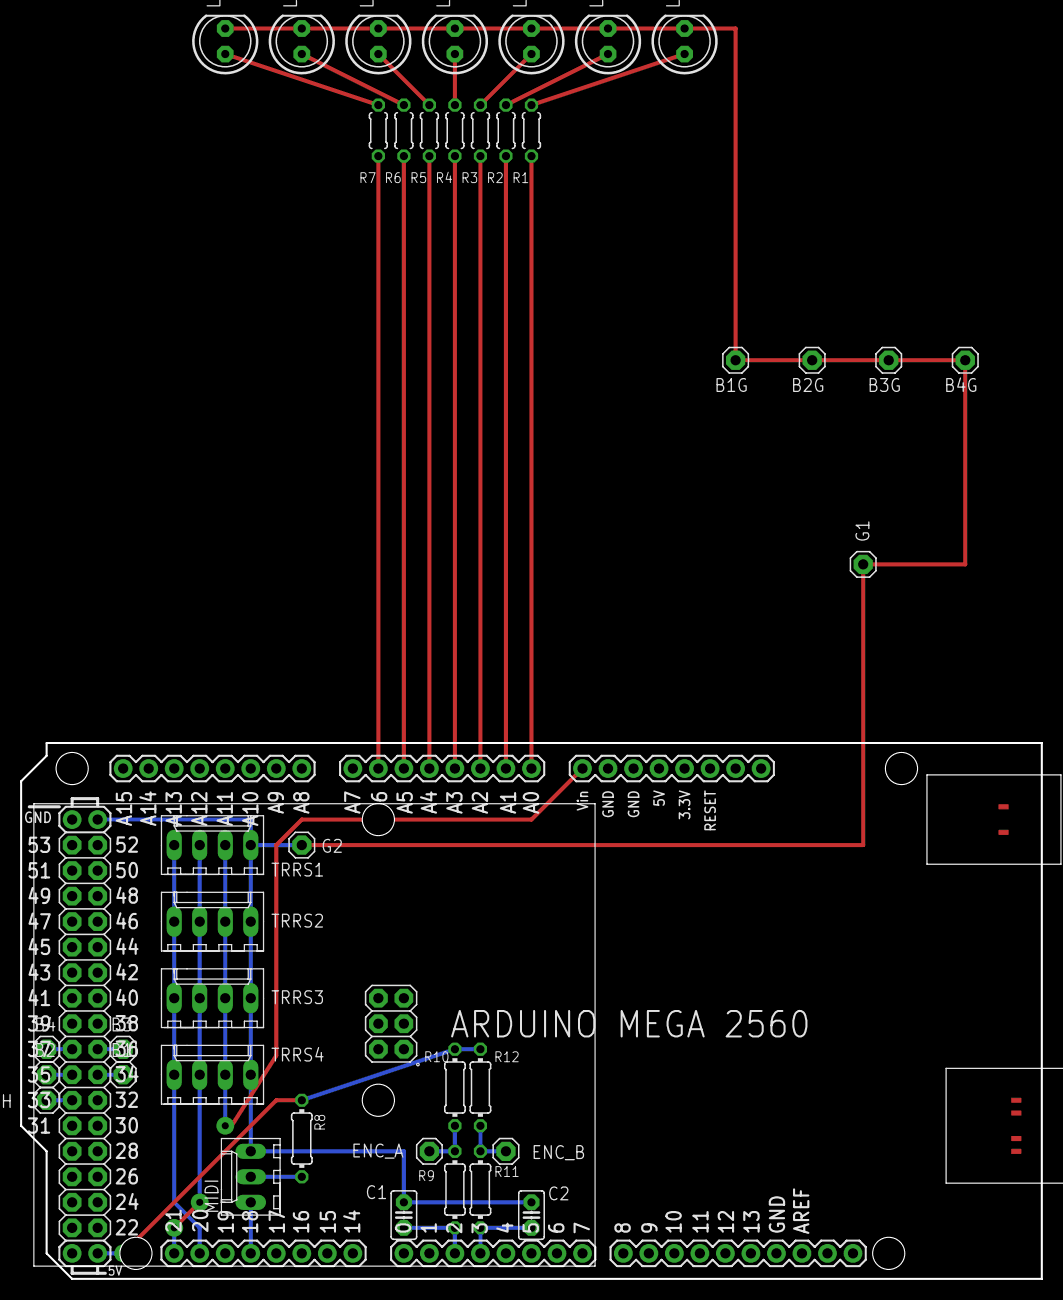
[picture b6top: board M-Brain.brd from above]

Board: 2 copper layers, 40 parts (0 on the bottom side), 30 nets.
